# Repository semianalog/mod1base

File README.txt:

MOD1BASE  [[WIP]]
=================

Work in progress.

Base/motherboard for MOD1 series of modular power supplies.

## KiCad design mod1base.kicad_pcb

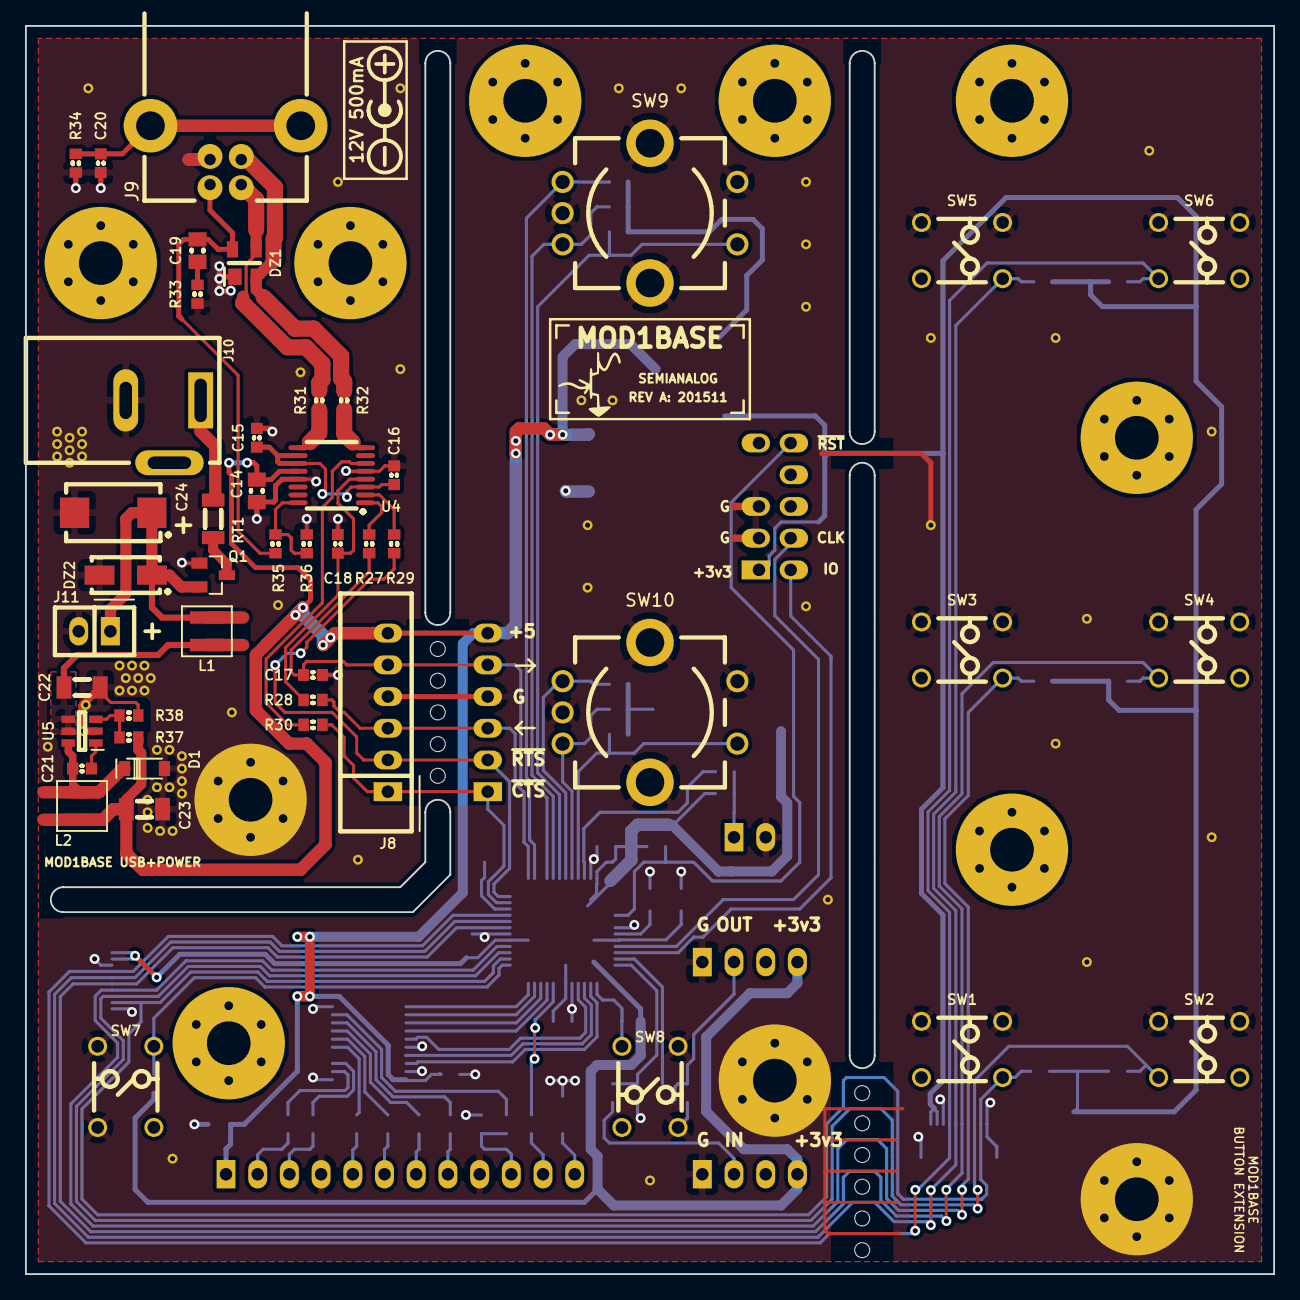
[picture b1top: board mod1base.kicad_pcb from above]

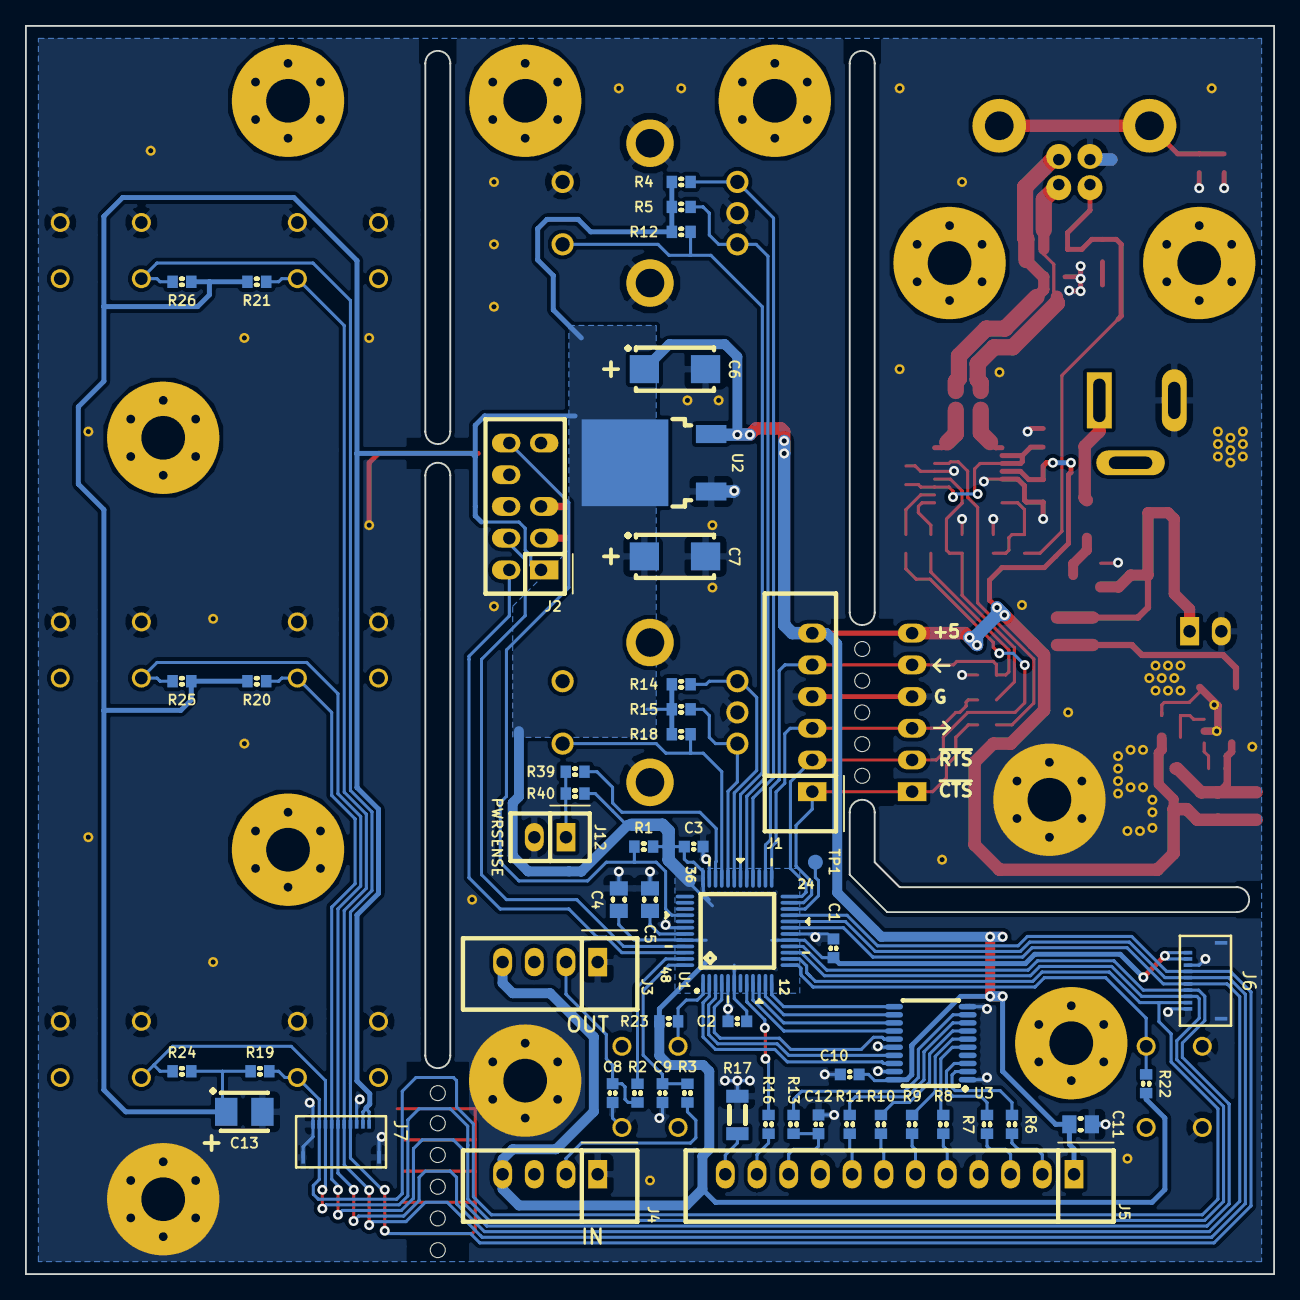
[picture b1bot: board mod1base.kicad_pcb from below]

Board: 2 copper layers, 100.0 x 100.0 mm, 110 parts (53 on the bottom side), 76 nets.

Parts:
C1, C2, C3, C10, C12, C15, C16, C21: 100n; CAPC1608X55
C4, C5, C11, C14, C19: 2u2; CAPC2012X70
C6, C7: 10u/25; CAPMP6032X280
C8, C9, C17, C18, C20: 220p; CAPC1608X55
C13: 6u8/10; CAPMP3528X210
C22, C23: 22u; CAPC3216X70
C24: 22u/25; CAPMP7343X310
D1: MBR0520; SOD-123
DZ1: DRTR5V0U2SR; SOT-143
DZ2: 1SMA5929BT3G; DIOM5226X203
J1, J8: COM; CONN-100MIL-M-1x6-SHROUD
J2: SWD; CONN-100MIL-M-2x5
J3: OUT; CONN-100MIL-M-1x4-SHROUD
J4: IN; CONN-100MIL-M-1x4-SHROUD
J5: LCD; CONN-100MIL-M-1x12-SHROUD
J6, J7: 5034801000; FFC
J9: USB; CONN-61729
J10: 12V 500mA; CONN-PJ-037A
J11: FAN; CONN-100MIL-M-1x2
J12: PWRSENSE; CONN-100MIL-M-1x2
L1, L2: 6u8; BOURNS-SRN3015
MP1, MP2, MP3, MP4, MP5, MP6, MP7, MP8, MP9, MP10, MP11: SCREW; SCREW-4-SUPPORTED
Q1: IRLML6402; SOT-23
R1, R4, R5, R12, R13, R14, R15, R16, R18, R19, R20, R21, R22, R23, R24, R25, R26, R35, R39, R40: 4k7; RESC1608X50
R2, R3, R6, R7, R8, R9, R10, R11, R27, R28, R29, R30: 100; RESC1608X50
R17: TBD; RESC3216X60
R31, R32, R33: 27; RESC1608X50
R34, R36, R37: 10k; RESC1608X50
R38: 1k91; RESC1608X50
RT1: 750mA; RESC3216X60
SW1: SOFT1; ESWITCH-TL1105
SW2: PRESETS; ESWITCH-TL1105
SW3, SW4: SOFT2; ESWITCH-TL1105
SW5: SOFT3; ESWITCH-TL1105
SW6: ALL_LOAD; ESWITCH-TL1105
SW7, SW8: STORE; ESWITCH-TL1105
SW9, SW10: EVE-JBBF2020B; PANASONIC-EVEJB
TP1: EXTRA; TEST-SMD-SMALL
U1: ATSAMD20G18A-AU; QFP50P900X900X120-48
U2: LM1117DT-3.3; TO-252
U3: 74HCT245PW; SOP65P640X110-20
U4: FT230XS; SOP63P600X160-16
U5: AP3211; SOT-23-6

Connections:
+3.3: C1.1, C2.1, C3.1, C4.1, C7.1, C13.1, J2.1, J3.4, J4.4, J6.9, J6.10, J7.9, J7.10, R1.1, R4.2, R5.2, R12.2, R14.2, R15.2, R18.2, R19.2, R20.2, R21.2, R22.2, R23.2, R24.2, R25.2, R26.2, R40.1, U1.6, U1.17, U1.36, U1.44, U2.3
+3.3A: C15.1, C16.1, U4.3, U4.10, U4.11
+5: C6.1, C10.1, C11.1, C14.1, C23.1, J1.6, J5.1, J8.6, L2.1, R37.1, U2.2, U3.20, U4.12
+12: C24.1, DZ2.1, J11.1, L1.2, Q1.2
/COM_IN: C9.1, R3.2, U1.48
/COM_OUT: R2.2, U1.47
/PWRSENSE: R39.2, U1.34
/Panel/5VLCD_CONT: C12.1, J5.10, R13.2
/Panel/5VLCD_D4: J5.5, R8.1
/Panel/5VLCD_D5: J5.6, R9.1
/Panel/5VLCD_D6: J5.7, R10.1
/Panel/5VLCD_D7: J5.8, R11.1
/Panel/5VLCD_D_~C: J5.2, R6.1
/Panel/5VLCD_E: J5.3, R7.1
/Panel/5VLCD_LEDK: J5.12, R17.1
/Panel/5VVFD_BUSY: J5.11, R16.2
/Panel/LCD_CONT: U1.12, U3.11
/Panel/LCD_D4: U1.4, U3.15
/Panel/LCD_D5: U1.9, U3.14
/Panel/LCD_D6: U1.10, U3.13
/Panel/LCD_D7: U1.11, U3.12
/Panel/LCD_D_~C: U1.2, U3.18
/Panel/LCD_E: U1.3, U3.17
/Panel/VFD_BUSY: R16.1, U1.8
/ROT0: R5.1, SW9.1, U1.29
/ROT1: R4.1, SW9.3, U1.28
/ROT2: R12.1, SW9.4, U1.30
/ROT3: R15.1, SW10.1, U1.32
/ROT4: R14.1, SW10.3, U1.31
/ROT5: R18.1, SW10.4, U1.33
/Rear breakaway/5VFB: R37.2, R38.1, U5.3
/Rear breakaway/5VIN: C22.1, L1.1, U5.4, U5.5
/Rear breakaway/5VSW: C21.1, D1.1, L2.2, U5.6
/Rear breakaway/D+: R32.1, U4.8
/Rear breakaway/D-: R31.1, U4.9
/Rear breakaway/FROM_USB: C17.1, J1.5, J8.5, R27.1, U1.26
/Rear breakaway/TO_USB: J1.3, J8.3, R28.1, U1.25
/Rear breakaway/USBD+: DZ1.2, J9.3, R32.2
/Rear breakaway/USBD-: DZ1.3, J9.2, R31.2
/Rear breakaway/VBSENSE_FTDI: R35.2, R36.1, U4.16
/Rear breakaway/~CTS: J1.1, J8.1, R30.1, U1.23
/Rear breakaway/~RTS: J1.2, J8.2, R29.1, U1.24
/SW1: J6.2, J7.2, R19.1, SW1.3, U1.14
/SW2: J6.3, J7.3, R24.1, SW2.1, U1.15
/SW3: J6.4, J7.4, R20.1, SW3.3, U1.16
/SW4: J6.5, J7.5, R25.1, SW4.1, U1.19
/SW5: J6.6, J7.6, R21.1, SW5.3, U1.20
/SW6: J6.7, J7.7, R26.1, SW6.1, U1.21
/SW7: R22.1, SW7.3, U1.13
/SW8: R23.1, SW8.1, U1.1
/SWCLK: J2.4, U1.45
/SWDIO: J2.2, U1.46
/VCORE: C5.1, U1.43
/~RST: J2.10, R1.2, U1.40
GND: C1.2, C2.2, C3.2, C4.2, C5.2, C6.2, C7.2, C8.2, C9.2, C10.2, C11.2, C12.2, C13.2, C14.2, C15.2, C16.2, C17.2, C18.2, C20.2, C22.2, C23.2, C24.2, D1.2, DZ1.1, DZ2.2, J1.4, J2.3, J2.5, J3.1, J4.1, J5.4, J5.9, J6.1, J6.8, J7.1, J7.8, J8.4, J9.4, J10.2, J11.2, J12.2, MP2.1, MP5.1, MP11.1, Q1.1, R17.2, R33.1, R34.2, R36.2, R38.2, SW1.2, SW1.4, SW2.2, SW2.4, SW3.2, SW3.4, SW4.2, SW4.4, SW5.2, SW5.4, SW6.2, SW6.4, SW7.2, SW7.4, SW8.2, SW8.4, SW9.2, SW9.5, SW10.2, SW10.5, U1.5, U1.18, U1.35, U1.42, U2.1, U3.1, U3.10, U3.16, U3.19, U4.5, U4.13, U5.2
unnamed: C8.1, J3.2, R2.1
unnamed: C18.1, R28.2, U4.4
unnamed: C19.2, R33.2
unnamed: C20.1, J9.SH, R34.1
unnamed: C21.2, U5.1
unnamed: J4.2, R3.1
unnamed: J10.1, RT1.2
unnamed: J12.1, R39.1, R40.2
unnamed: Q1.3, RT1.1
unnamed: R6.2, U3.2
unnamed: R7.2, U3.3
unnamed: R8.2, U3.5
unnamed: R9.2, U3.6
unnamed: R10.2, U3.7
unnamed: R11.2, U3.8
unnamed: R13.1, U3.9
unnamed: R27.2, U4.1
unnamed: R29.2, U4.2
unnamed: R30.2, U4.6
unnamed: TP1.1, U1.22
VBUS: C19.1, DZ1.4, J9.1, R35.1

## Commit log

2015-11-18 Add readme and license
2015-11-18 Rewrite references
2015-11-18 More finalization
2015-11-18 Ignore autosaves
2015-11-18 More layout work
2015-11-19 More PCB revision (fab candidate)
2015-11-19 Fab RC 2
2015-11-20 Finalize revision A
2015-11-28 Update BOM references
